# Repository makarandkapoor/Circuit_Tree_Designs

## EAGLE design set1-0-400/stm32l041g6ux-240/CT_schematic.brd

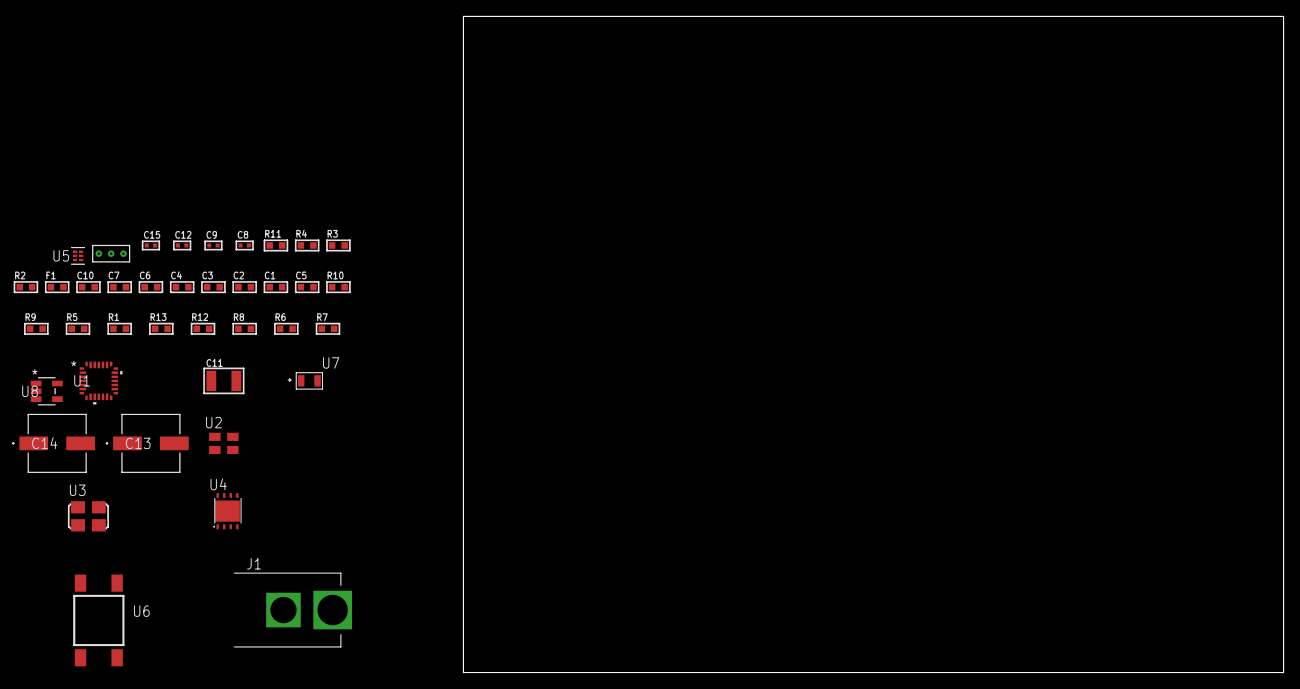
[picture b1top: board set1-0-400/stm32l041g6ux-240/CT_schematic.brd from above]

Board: 2 copper layers, 100.0 x 80.0 mm, 39 parts (0 on the bottom side), 18 nets, no tracks yet.

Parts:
C1, C2, C3, C4: 1e-07; C0603
C5: 4.7e-06; C0603
C6: 1e-08; C0603
C7, C10: 1e-06; C0603
C8, C9, C15: 1e-08; C0402
C11: 1e-05; C1210
C12: 1e-07; C0402
C13, C14: 0.0001; EXV-9H
F1: 240.0; L0603
J1: PJ-037B; PJ-037B_PACKAGE
R1, R5, R9, R10: 10000.0; R0603
R2: 1000.0; R0603
R3: 1600.5; R0603
R4: 4700.0; R0603
R6, R8: 100000.0; R0603
R7: 153694.38; R0603
R11: 9100.0; R0603
R12: 680000.0; R0603
R13: 120000.0; R0603
U1: STM32L041G6U7; UFQFPN28
U2: ASEK-32.768KHz-ECST; ASEK
U3: ASFL1-12MHZ-NCS; ASFL1
U4: LP2951ACSDX/NOPB; WSON-8
U5: TPS3895ADRYR; SON-6
U6: 4-1437565-2; SW_4-1437565-2
U7: Q65110A2395; LGM67K-G1J2-24-Z
U8: nc7sz125m5x; NC7SZ125M5X
U9: Dummy; DUMMY_PACKAGE_78

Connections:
CLK_U1_2: U1.2, U2.3
CLK_U1_6: U1.6, U3.3
GND: C1.2, C2.2, C3.2, C4.2, C5.2, C6.2, C7.2, C8.2, C9.2, C10.2, C11.2, C12.2, C13.2, C14.2, C15.2, J1.2, R2.2, R5.2, R8.2, R11.2, R13.2, U1.16, U1.28, U2.2, U3.2, U4.3, U4.4, U4.PAD, U5.2, U7.C, U8.1, U8.3, U9.1
NET_U1_4: R4.1, U1.4, U8.4
NET_U1_5: C6.1, C7.1, F1.1, U1.5
NET_U1_25: R3.1, U1.25, U7.A
NET_U1_26: R1.1, U1.26, U6.3, U6.4
NET_U1_27: R5.1, U1.27
NET_U4_5: R6.1, U4.5
NET_U4_7: R7.2, R8.1, U4.7
NET_U5_1: R10.1, R11.1, U5.1
NET_U5_3: R12.2, R13.1, U5.3
NET_U5_4: R9.1, U5.4, U8.2
NET_U6_1: R2.1, U6.1, U6.2
PROC_ADC_IN4: U1.10, U9.2
PROC_ADC_IN6: U1.12, U9.3
VCC_S1_5V9: C10.1, C13.1, C14.1, J1.1, U4.8
VCC_TIER1_3V3: C1.1, C2.1, C3.1, C4.1, C5.1, C8.1, C9.1, C11.1, C12.1, C15.1, F1.2, R1.2, R3.2, R4.2, R6.2, R7.1, R9.2, R10.2, R12.1, U1.1, U1.17, U2.4, U3.4, U4.1, U5.6, U8.5

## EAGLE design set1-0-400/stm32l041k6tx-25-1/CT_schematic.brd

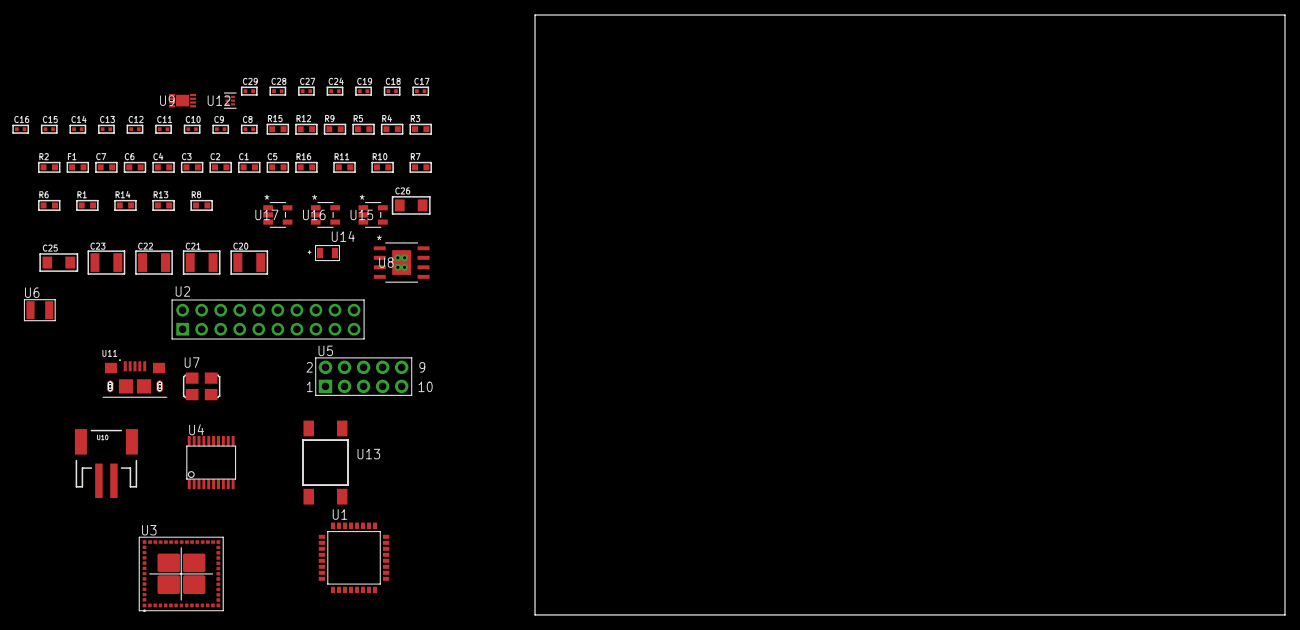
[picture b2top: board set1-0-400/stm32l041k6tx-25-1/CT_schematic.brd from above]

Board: 2 copper layers, 156.9 x 80.0 mm, 63 parts (0 on the bottom side), 41 nets, no tracks yet.

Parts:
C1, C2, C3, C4: 1e-07; C0603
C5: 4.7e-06; C0603
C6: 1e-08; C0603
C7: 1e-06; C0603
C8, C9: 1e-11; C0402
C10, C11, C12, C13, C14, C15, C16, C17, C18, C24: 1e-07; C0402
C19, C27, C28, C29: 1e-08; C0402
C20, C21, C22, C23: 1e-05; C1210
C25, C26: 1e-05; C1206
F1: 240.0; L0603
R1, R6, R7, R10, R11, R16: 10000.0; R0603
R2: 1000.0; R0603
R3: 1600.5; R0603
R4, R5: 4700.0; R0603
R8: 4031.5447154472; R0603
R9: 2200.0; R0603
R12: 9100.0; R0603
R13: 680000.0; R0603
R14: 120000.0; R0603
R15: 2000.0; R0603
U1: STM32L041K6T7; LQFP32
U2: TST-110-05-T-D-RA
U3: MBH7BLZ02-109004
U4: SP3203ECY-L/TR; TSSOP20-I
U5: HTSS-105-01-G-D
U6: ABS07-32.768KHZ-7-T
U7: ASFL1-12MHZ-NCS; ASFL1
U8: MIC5234YME; SOIC-8_EP
U9: MCP73831T-2ACI/MC; DFN8_2X3MC
U10: S2B-PH-SM4-TB(LF)(SN); JST-2-SMD
U11: 10118193-0001LF; FCI_10118193-0001LF
U12: TPS3895ADRYR; SON-6
U13: 4-1437565-2; SW_4-1437565-2
U14: Q65110A2395; LGM67K-G1J2-24-Z
U15, U16, U17: nc7sz125m5x; NC7SZ125M5X

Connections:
CLK_CRYSTAL_U1_2: C8.1, U1.2, U6.1
CLK_CRYSTAL_U1_3: C9.1, U1.3, U6.2
CLK_U1_6: U1.6, U7.3
GND: C1.2, C2.2, C3.2, C4.2, C5.2, C6.2, C7.2, C8.2, C9.2, C10.2, C11.2, C12.2, C13.2, C14.2, C17.2, C18.2, C19.2, C20.2, C21.2, C22.2, C23.2, C24.2, C25.2, C26.2, C27.2, C28.2, C29.2, R2.2, R6.2, R9.2, R12.2, R14.2, R15.2, U1.16, U1.32, U2.4, U2.6, U2.8, U2.10, U2.12, U2.14, U2.16, U2.18, U2.20, U3.1, U3.3, U3.15, U3.27, U3.29, U3.41, U3.42, U3.43, U3.44, U3.45, U3.46, U3.47, U3.48, U3.49, U3.50, U3.52, U3.53, U3.54, U3.55, U3.56, U4.18, U5.9, U7.2, U8.7, U8.EPAD, U9.6, U9.9, U10.2, U11.5, U11.6, U11.7, U11.8, U11.9, U12.2, U14.C, U15.2, U15.3, U16.1, U16.3, U17.1, U17.3
INPUT_USBPOWER_5V: C25.1, R16.2, U9.1, U9.2, U11.1
NET_U1_4: R5.1, U1.4, U17.4
NET_U1_5: C6.1, C7.1, F1.1, U1.5
NET_U1_29: R3.1, U1.29, U14.A
NET_U1_30: R1.1, U1.30, U13.3, U13.4
NET_U1_31: R6.1, U1.31
NET_U3_39: R4.1, U3.39, U16.4
NET_U4_1: C15.1, U4.1
NET_U4_2: C17.1, U4.2
NET_U4_3: C15.2, U4.3
NET_U4_4: C16.1, U4.4
NET_U4_5: C16.2, U4.5
NET_U4_6: C18.1, U4.6
NET_U5_3: U4.14, U5.3
NET_U5_4: U4.13, U5.4
NET_U5_5: U4.17, U5.5
NET_U5_6: U4.16, U5.6
NET_U8_4: R8.2, R9.1, U8.4
NET_U9_5: R16.1, U9.5
NET_U9_8: R15.1, U9.8
NET_U12_1: R11.1, R12.1, U12.1
NET_U12_3: R13.2, R14.1, U12.3
NET_U12_4: R10.1, U12.4, U15.4, U16.2, U17.2
NET_U13_1: R2.1, U13.1, U13.2
PROC_LPUART1_CTS: U1.12, U3.26
PROC_LPUART1_RTS: U1.15, U3.24
PROC_LPUART1_RX: U1.9, U3.25
PROC_LPUART1_TX: U1.8, U3.23
PROC_SYS_SWCLK: U1.24, U2.9
PROC_SYS_SWDIO: U1.23, U2.7
PROC_USART2_CTS: U1.13, U4.8
PROC_USART2_RTS: U1.7, U4.10
PROC_USART2_RX: U1.20, U4.11
PROC_USART2_TX: U1.19, U4.7
RST_OUT_U2_SRESET_B: R7.1, U2.15, U15.1
VCC_S1_3V7: C20.1, C21.1, C26.1, U8.5, U8.8, U9.3, U9.4, U10.1
VCC_TIER1_3V3: C1.1, C2.1, C3.1, C4.1, C5.1, C10.1, C11.1, C12.1, C13.1, C14.1, C19.1, C22.1, C23.1, C24.1, C27.1, C28.1, C29.1, F1.2, R1.2, R3.2, R4.2, R5.2, R7.2, R8.1, R10.2, R11.2, R13.1, U1.1, U1.17, U2.1, U3.28, U4.12, U4.19, U7.4, U8.1, U12.6, U15.5, U16.5, U17.5

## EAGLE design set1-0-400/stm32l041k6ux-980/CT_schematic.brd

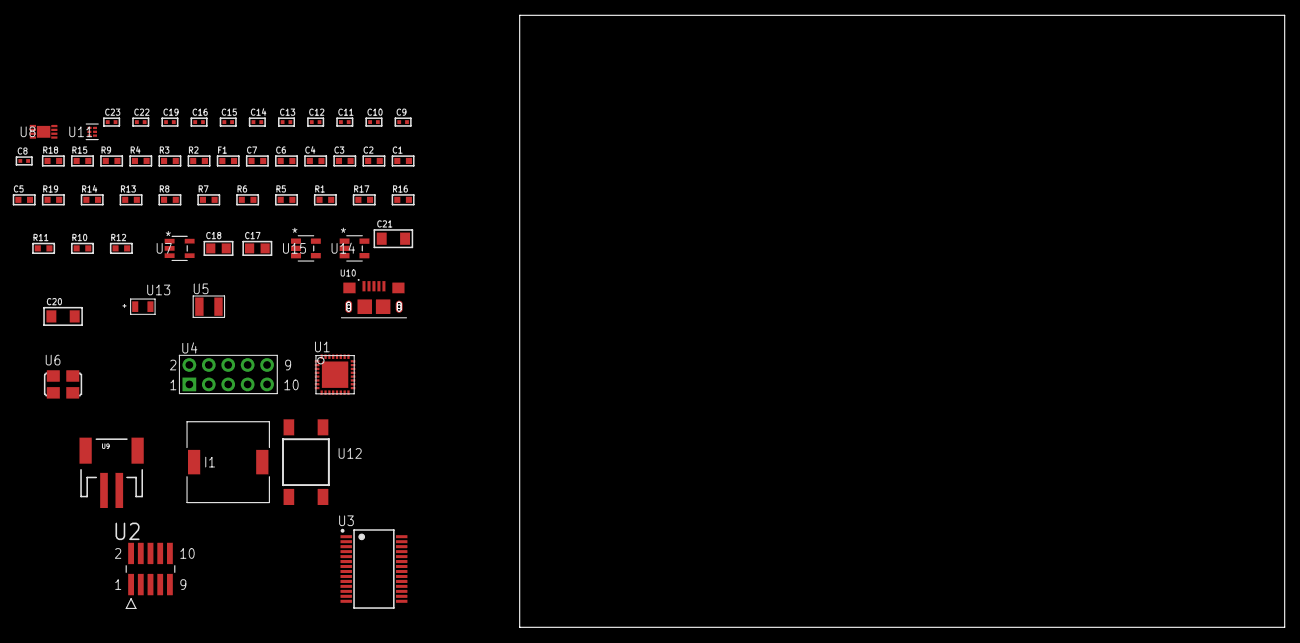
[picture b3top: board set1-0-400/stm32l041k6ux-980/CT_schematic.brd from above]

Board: 2 copper layers, 122.6 x 80.0 mm, 59 parts (0 on the bottom side), 40 nets, no tracks yet.

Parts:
C1, C2, C3, C4: 1e-07; C0603
C5: 4.7e-06; C0603
C6: 1e-08; C0603
C7: 1e-06; C0603
C8, C9: 1e-11; C0402
C10, C11, C12, C13, C14, C15, C19: 1e-07; C0402
C16, C22, C23: 1e-08; C0402
C17, C18: 1e-05; C0805
C20, C21: 1e-05; C1206
F1: 240.0; L0603
I1: 5.2e-06; DR1040
R1, R5, R6, R7, R8, R13, R14, R19: 10000.0; R0603
R2: 1000.0; R0603
R3: 1600.5; R0603
R4: 4700.0; R0603
R9: 5.0; R0603
R10: 100000.0; R0603
R11: 220000.0; R0603
R12: 1000000.0; R0603
R15: 9100.0; R0603
R16: 680000.0; R0603
R17: 120000.0; R0603
R18: 2000.0; R0603
U1: stm32l041K6U7; UFQFPN32
U2: FTSH-105-01-L-DV-K; SAMTEC_FTSH-105-01-L-DV-K
U3: ST3241EBPR; SSOP-28
U4: HTSS-105-01-G-D
U5: ABS07-32.768KHZ-7-T
U6: ASFL1-12MHZ-NCS; ASFL1
U7: ltc3406es5; TSOT-23-5
U8: MCP73831T-2ACI/MC; DFN8_2X3MC
U9: S2B-PH-SM4-TB(LF)(SN); JST-2-SMD
U10: 10118193-0001LF; FCI_10118193-0001LF
U11: TPS3895ADRYR; SON-6
U12: 4-1437565-2; SW_4-1437565-2
U13: Q65110A2395; LGM67K-G1J2-24-Z
U14, U15: nc7sz125m5x; NC7SZ125M5X

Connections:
CLK_CRYSTAL_U1_2: C8.1, U1.2, U5.1
CLK_CRYSTAL_U1_3: C9.1, U1.3, U5.2
CLK_U1_6: U1.6, U6.3
GND: C1.2, C2.2, C3.2, C4.2, C5.2, C6.2, C7.2, C8.2, C9.2, C10.2, C11.2, C14.2, C15.2, C16.2, C17.2, C18.1, C18.2, C19.2, C20.2, C21.2, C22.2, C23.2, R2.2, R5.2, R9.2, R11.2, R15.2, R17.2, R18.2, U1.EPAD, U2.3, U2.5, U3.23, U3.25, U4.9, U6.2, U7.2, U8.6, U8.9, U9.2, U10.5, U10.6, U10.7, U10.8, U10.9, U11.2, U13.C, U14.2, U14.3, U15.1, U15.3
INPUT_USBPOWER_5V: C20.1, R19.2, U8.1, U8.2, U10.1
NET_U1_4: R4.1, U1.4, U15.4
NET_U1_5: C6.1, C7.1, F1.1, U1.5
NET_U1_30: R3.1, U1.30, U13.A
NET_U1_31: R5.1, U1.31
NET_U1_32: R1.1, U1.32, U12.3, U12.4
NET_U2_9: R9.1, U2.9
NET_U3_1: C13.1, U3.1
NET_U3_2: C13.2, U3.2
NET_U3_3: C15.1, U3.3
NET_U3_22: R10.1, U3.22
NET_U3_24: C12.2, U3.24
NET_U3_27: C14.1, U3.27
NET_U3_28: C12.1, U3.28
NET_U4_3: U3.4, U4.3
NET_U4_4: U3.5, U4.4
NET_U4_5: U3.9, U4.5
NET_U4_6: U3.10, U4.6
NET_U7_3: I1.1, U7.3
NET_U7_5: R11.1, R12.1, U7.5
NET_U7_ATNET_3: I1.2, R12.2
NET_U8_5: R19.1, U8.5
NET_U8_8: R18.1, U8.8
NET_U11_1: R14.1, R15.1, U11.1
NET_U11_3: R16.2, R17.1, U11.3
NET_U11_4: R13.1, U11.4, U14.4, U15.2
NET_U12_1: R2.1, U12.1, U12.2
PROC_LPUART1_CTS: U1.12, U3.13
PROC_LPUART1_RTS: U1.15, U3.18
PROC_LPUART1_RX: U1.9, U3.19
PROC_LPUART1_TX: U1.8, U3.14
PROC_SYS_SWCLK: R7.1, U1.24, U2.4
PROC_SYS_SWDIO: R8.1, U1.23, U2.2
RST_OUT_U2_JTAG_RST_B: R6.1, U2.10, U14.1
VCC_S1_3V7: C17.1, C21.1, U7.4, U8.3, U8.4, U9.1
VCC_TIER1_3V3: C1.1, C2.1, C3.1, C4.1, C5.1, C10.1, C11.1, C16.1, C18.2, C19.1, C22.1, C23.1, F1.2, I1.2, R1.2, R3.2, R4.2, R6.2, R7.2, R8.2, R10.2, R12.2, R13.2, R14.2, R16.1, U1.1, U1.17, U2.1, U3.26, U6.4, U11.6, U14.5, U15.5

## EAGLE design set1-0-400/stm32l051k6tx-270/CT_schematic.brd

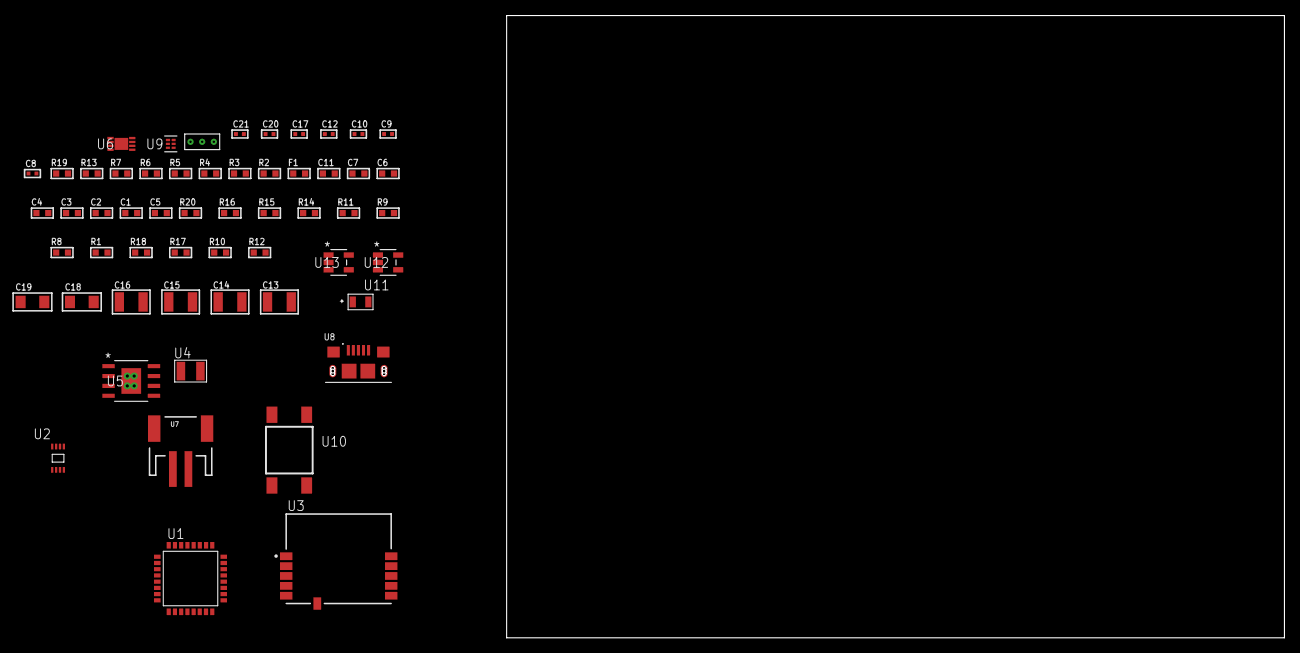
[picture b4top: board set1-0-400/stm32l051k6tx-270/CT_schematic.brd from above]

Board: 2 copper layers, 122.6 x 80.0 mm, 56 parts (0 on the bottom side), 28 nets, no tracks yet.

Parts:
C1, C2, C3, C4: 1e-07; C0603
C5: 4.7e-06; C0603
C6: 1e-08; C0603
C7, C11: 1e-06; C0603
C8, C9: 1e-11; C0402
C10, C20, C21: 1e-08; C0402
C12, C17: 1e-07; C0402
C13, C14, C15, C16: 1e-05; C1210
C18, C19: 1e-05; C1206
F1: 240.0; L0603
R1, R8, R9, R14, R15, R20: 10000.0; R0603
R2: 1000.0; R0603
R3: 910.0; R0603
R4, R5: 4700.0; R0603
R6, R7, R13: 2200.0; R0603
R10: 100000.0; R0603
R11: 47000.0; R0603
R12: 1402.2764227642; R0603
R16: 82000.0; R0603
R17: 300000.0; R0603
R18: 120000.0; R0603
R19: 2000.0; R0603
U1: STM32L051K6T6; LQFP32
U2: 24AA00T-I/MNY; TDFN-8/6MM
U3: SPBTLE-RF; XCVR_SPBTLE-RF
U4: ABS07-32.768KHZ-7-T
U5: MIC5234YME; SOIC-8_EP
U6: MCP73831T-2ACI/MC; DFN8_2X3MC
U7: S2B-PH-SM4-TB(LF)(SN); JST-2-SMD
U8: 10118193-0001LF; FCI_10118193-0001LF
U9: TPS3895ADRYR; SON-6
U10: 4-1437565-2; SW_4-1437565-2
U11: Q65110A2395; LGM67K-G1J2-24-Z
U12, U13: nc7sz125m5x; NC7SZ125M5X
U14: Dummy; DUMMY_PACKAGE_116

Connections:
CLK_CRYSTAL_U1_2: C8.1, U1.2, U4.1
CLK_CRYSTAL_U1_3: C9.1, U1.3, U4.2
GND: C1.2, C2.2, C3.2, C4.2, C5.2, C6.2, C7.2, C8.2, C9.2, C10.2, C11.2, C12.2, C13.2, C14.2, C15.2, C16.2, C17.2, C18.2, C19.2, C20.2, C21.2, R2.2, R8.2, R10.2, R11.2, R13.2, R16.2, R18.2, R19.2, U1.16, U1.32, U2.4, U3.6, U5.7, U5.EPAD, U6.6, U6.9, U7.2, U8.5, U8.6, U8.7, U8.8, U8.9, U9.2, U11.C, U12.1, U12.3, U13.1, U13.3, U14.1
INPUT_USBPOWER_5V: C18.1, R20.2, U6.1, U6.2, U8.1
NET_U1_4: R5.1, U1.4, U13.4
NET_U1_5: C6.1, C7.1, F1.1, U1.5
NET_U1_27: R3.1, U1.27, U11.A
NET_U1_28: R1.1, U1.28, U10.3, U10.4
NET_U1_29: R6.1, U1.29, U2.6
NET_U1_30: R7.1, U1.30, U2.5
NET_U1_31: R8.1, U1.31
NET_U3_11: R4.1, U3.11, U12.4
NET_U5_4: R12.2, R13.1, U5.4
NET_U6_5: R20.1, U6.5
NET_U6_8: R19.1, U6.8
NET_U9_1: R15.1, R16.1, U9.1
NET_U9_3: R17.2, R18.1, U9.3
NET_U9_4: R14.1, U9.4, U12.2, U13.2
NET_U10_1: R2.1, U10.1, U10.2
PROC_GPIO_TO_U3_SPI_IRQ: R11.1, U1.6, U3.4
PROC_SPI1_MISO: U1.12, U3.8
PROC_SPI1_MOSI: U1.13, U3.9
PROC_SPI1_NSS: R9.1, U1.10, U3.10
PROC_SPI1_SCK: R10.1, U1.11, U3.7
PROC_TIM2_CH3: U1.8, U14.3
PROC_TIM2_CH4: U1.9, U14.2
VCC_S1_3V7: C13.1, C14.1, C19.1, U5.5, U5.8, U6.3, U6.4, U7.1
VCC_TIER1_1V8: C1.1, C2.1, C3.1, C4.1, C5.1, C10.1, C11.1, C12.1, C15.1, C16.1, C17.1, C20.1, C21.1, F1.2, R1.2, R3.2, R4.2, R5.2, R6.2, R7.2, R9.2, R12.1, R14.2, R15.2, R17.1, U1.1, U1.17, U2.8, U3.5, U5.1, U9.6, U12.5, U13.5

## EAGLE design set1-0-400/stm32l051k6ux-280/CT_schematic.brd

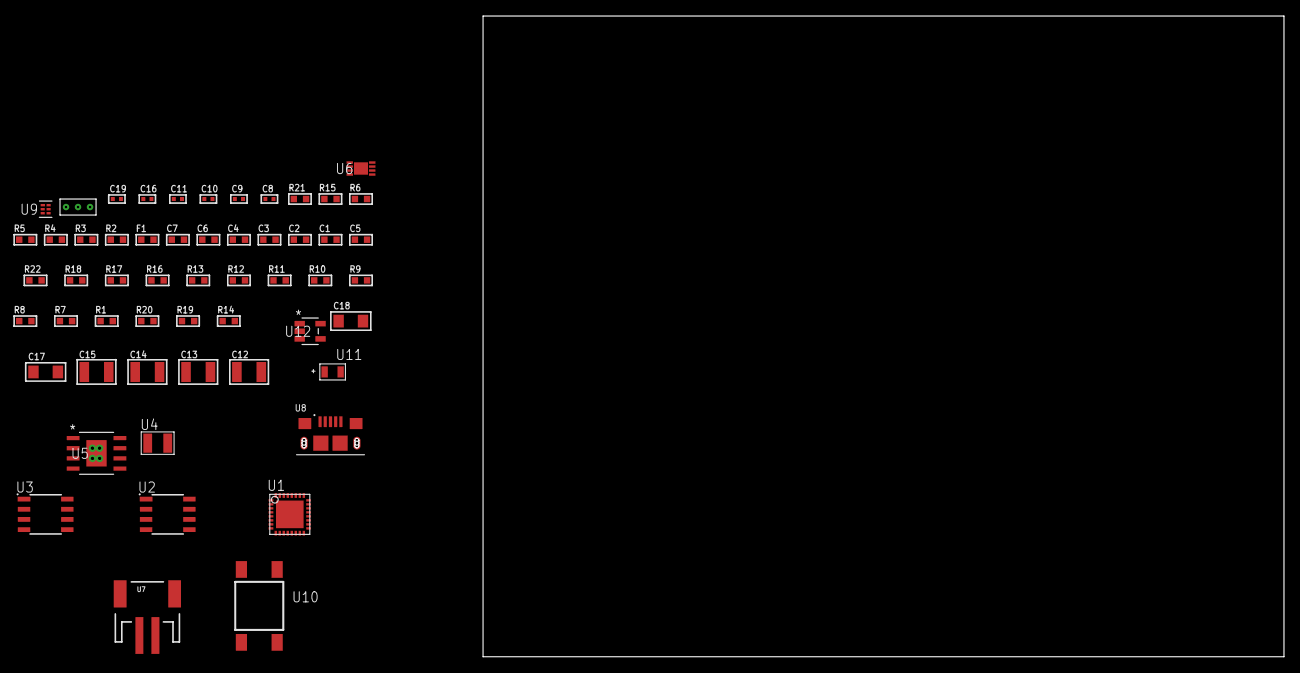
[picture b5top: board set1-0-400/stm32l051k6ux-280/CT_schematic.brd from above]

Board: 2 copper layers, 122.6 x 80.0 mm, 55 parts (0 on the bottom side), 31 nets, no tracks yet.

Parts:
C1, C2, C3, C4: 1e-07; C0603
C5: 4.7e-06; C0603
C6: 1e-08; C0603
C7: 1e-06; C0603
C8, C9: 1e-11; C0402
C10, C11, C19: 1e-08; C0402
C12, C13, C14, C15: 1e-05; C1210
C16: 1e-07; C0402
C17, C18: 1e-05; C1206
F1: 240.0; L0603
R1, R7, R8, R9, R10, R11, R12, R13, R16, R17, R22: 10000.0; R0603
R2: 1000.0; R0603
R3: 910.0; R0603
R4: 4700.0; R0603
R5, R6, R15: 2200.0; R0603
R14: 1402.2764227642; R0603
R18: 82000.0; R0603
R19: 300000.0; R0603
R20: 120000.0; R0603
R21: 2000.0; R0603
U1: STM32L051K6U6; UFQFPN32
U2: AT25080B-SSHL-T; SOIC-8
U3: 24AA1025T-I/SN; SOIC-8
U4: ABS07-32.768KHZ-7-T
U5: MIC5234YME; SOIC-8_EP
U6: MCP73831T-2ACI/MC; DFN8_2X3MC
U7: S2B-PH-SM4-TB(LF)(SN); JST-2-SMD
U8: 10118193-0001LF; FCI_10118193-0001LF
U9: TPS3895ADRYR; SON-6
U10: 4-1437565-2; SW_4-1437565-2
U11: Q65110A2395; LGM67K-G1J2-24-Z
U12: nc7sz125m5x; NC7SZ125M5X
U13: Dummy; DUMMY_PACKAGE_115

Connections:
CLK_CRYSTAL_U1_2: C8.1, U1.2, U4.1
CLK_CRYSTAL_U1_3: C9.1, U1.3, U4.2
GND: C1.2, C2.2, C3.2, C4.2, C5.2, C6.2, C7.2, C8.2, C9.2, C10.2, C11.2, C12.2, C13.2, C14.2, C15.2, C16.2, C17.2, C18.2, C19.2, R2.2, R7.2, R15.2, R18.2, R20.2, R21.2, U1.EPAD, U2.4, U3.4, U5.7, U5.EPAD, U6.6, U6.9, U7.2, U8.5, U8.6, U8.7, U8.8, U8.9, U9.2, U11.C, U12.1, U12.3, U13.1
INPUT_USBPOWER_5V: C17.1, R22.2, U6.1, U6.2, U8.1
NET_U1_4: R4.1, U1.4, U12.4
NET_U1_5: C6.1, C7.1, F1.1, U1.5
NET_U1_28: R3.1, U1.28, U11.A
NET_U1_29: R5.1, U1.29, U3.6
NET_U1_30: R6.1, U1.30, U3.5
NET_U1_31: R7.1, U1.31
NET_U1_32: R1.1, U1.32, U10.3, U10.4
NET_U2_3: R8.1, U2.3
NET_U2_7: R10.1, U2.7
NET_U3_1: R12.1, U3.1
NET_U3_2: R13.1, U3.2
NET_U3_3: R11.1, U3.3
NET_U5_4: R14.2, R15.1, U5.4
NET_U6_5: R22.1, U6.5
NET_U6_8: R21.1, U6.8
NET_U9_1: R17.1, R18.1, U9.1
NET_U9_3: R19.2, R20.1, U9.3
NET_U9_4: R16.1, U9.4, U12.2
NET_U10_1: R2.1, U10.1, U10.2
PROC_SPI1_MISO: U1.12, U2.2
PROC_SPI1_MOSI: U1.13, U2.5
PROC_SPI1_NSS: R9.1, U1.10, U2.1
PROC_SPI1_SCK: U1.11, U2.6
PROC_TIM2_CH3: U1.8, U13.3
PROC_TIM2_CH4: U1.9, U13.2
VCC_S1_3V7: C12.1, C13.1, C18.1, U5.5, U5.8, U6.3, U6.4, U7.1
VCC_TIER1_1V8: C1.1, C2.1, C3.1, C4.1, C5.1, C10.1, C11.1, C14.1, C15.1, C16.1, C19.1, F1.2, R1.2, R3.2, R4.2, R5.2, R6.2, R8.2, R9.2, R10.2, R11.2, R12.2, R13.2, R14.1, R16.2, R17.2, R19.1, U1.1, U1.17, U2.8, U3.7, U3.8, U5.1, U9.6, U12.5

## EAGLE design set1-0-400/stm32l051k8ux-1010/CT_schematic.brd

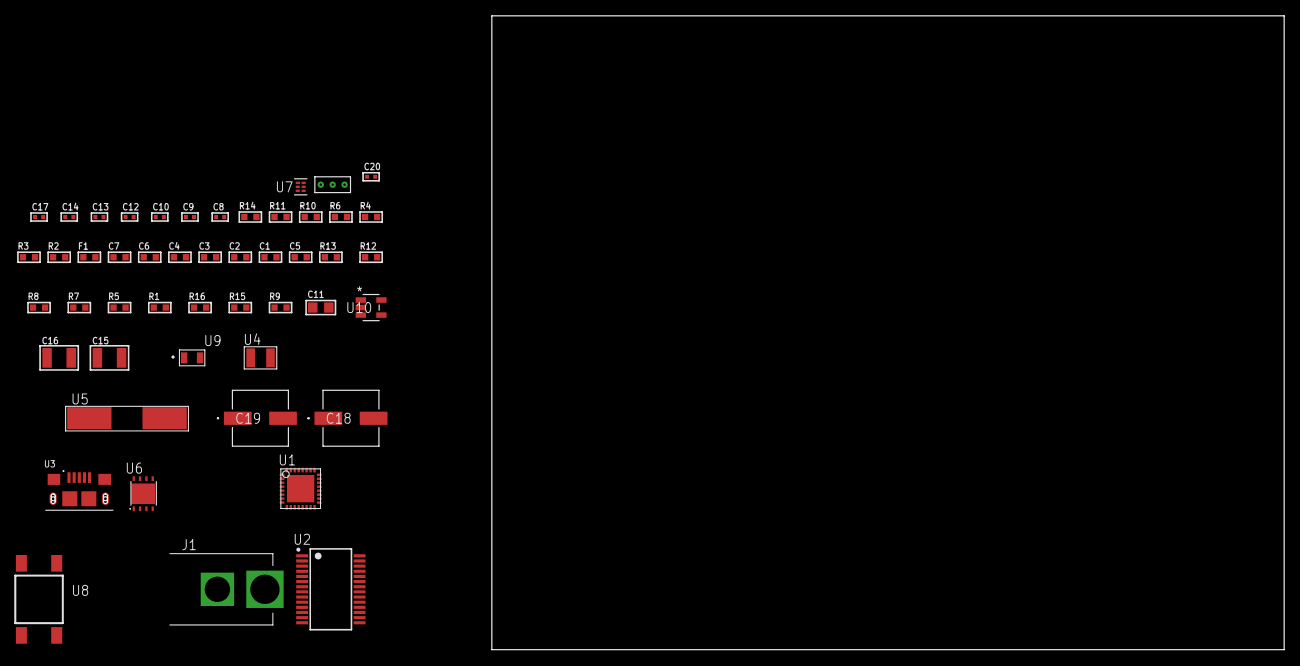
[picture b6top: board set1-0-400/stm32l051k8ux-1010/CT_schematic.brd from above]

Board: 2 copper layers, 155.6 x 80.0 mm, 49 parts (0 on the bottom side), 31 nets, no tracks yet.

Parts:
C1, C2, C3, C4: 1e-07; C0603
C5: 4.7e-06; C0603
C6: 1e-08; C0603
C7: 1e-06; C0603
C8, C9: 1e-11; C0402
C10, C12, C13, C17: 1e-07; C0402
C11: 4.7e-06; C0805
C14, C20: 1e-08; C0402
C15, C16: 1e-05; C1210
C18, C19: 0.0001; EXV-9H
F1: 240.0; L0603
J1: PJ-037B; PJ-037B_PACKAGE
R1, R5, R7, R8, R12, R13: 10000.0; R0603
R2, R11: 1000.0; R0603
R3: 1600.5; R0603
R4, R6: 4700.0; R0603
R9: 100000.0; R0603
R10: 2231.0; R0603
R14: 9100.0; R0603
R15: 680000.0; R0603
R16: 120000.0; R0603
U1: STM32L051K8U3; UFQFPN32
U2: FT232RL-REEL; SSOP-28
U3: 10118193-0001LF; FCI_10118193-0001LF
U4: ABS07-32.768KHZ-7-T
U5: ABLS-12.000MHZ-B4-T
U6: LP3878SDX-ADJ/NOPB; WSON-8
U7: TPS3895ADRYR; SON-6
U8: 4-1437565-2; SW_4-1437565-2
U9: Q65110A2395; LGM67K-G1J2-24-Z
U10: nc7sz125m5x; NC7SZ125M5X
U11: Dummy; DUMMY_PACKAGE_97

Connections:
CLK_CRYSTAL_U1_2: C8.1, U1.2, U4.1
CLK_CRYSTAL_U1_3: C9.1, U1.3, U4.2
CLK_CRYSTAL_U2_27: U2.27, U5.1
CLK_CRYSTAL_U2_28: U2.28, U5.2
GND: C1.2, C2.2, C3.2, C4.2, C5.2, C6.2, C7.2, C8.2, C9.2, C10.2, C11.2, C12.2, C13.2, C14.2, C15.2, C16.2, C17.2, C18.2, C19.2, C20.2, J1.2, R2.2, R5.2, R8.2, R11.2, R14.2, R16.2, U1.EPAD, U2.7, U2.18, U2.21, U2.25, U2.26, U3.5, U3.6, U3.7, U3.8, U3.9, U6.3, U6.PAD, U7.2, U9.C, U10.1, U10.3, U11.1
NET_U1_4: R4.1, U1.4, U10.4
NET_U1_5: C6.1, C7.1, F1.1, U1.5
NET_U1_30: R3.1, U1.30, U9.A
NET_U1_31: R5.1, U1.31
NET_U1_32: R1.1, U1.32, U8.3, U8.4
NET_U2_14: R7.1, U2.14
NET_U2_17: C12.1, U2.17
NET_U2_19: R8.1, U2.19
NET_U3_1: R6.1, U3.1
NET_U3_2: U2.16, U3.2
NET_U3_3: U2.15, U3.3
NET_U6_1: C14.1, U6.1
NET_U6_6: R10.2, R11.1, U6.6
NET_U6_8: R9.1, U6.8
NET_U7_1: R13.1, R14.1, U7.1
NET_U7_3: R15.2, R16.1, U7.3
NET_U7_4: R12.1, U7.4, U10.2
NET_U8_1: R2.1, U8.1, U8.2
PROC_ADC_IN4: U1.10, U11.2
PROC_ADC_IN6: U1.12, U11.3
PROC_USART1_CTS: U1.21, U2.3
PROC_USART1_RTS: U1.22, U2.11
PROC_USART1_RX: U1.20, U2.1
PROC_USART1_TX: U1.19, U2.5
VCC_S1_13V6: C15.1, C18.1, C19.1, J1.1, R9.2, U6.4
VCC_TIER1_3V3: C1.1, C2.1, C3.1, C4.1, C5.1, C10.1, C11.1, C13.1, C16.1, C17.1, C20.1, F1.2, R1.2, R3.2, R4.2, R7.2, R10.1, R12.2, R13.2, R15.1, U1.1, U1.17, U2.4, U2.20, U6.5, U7.6, U10.5

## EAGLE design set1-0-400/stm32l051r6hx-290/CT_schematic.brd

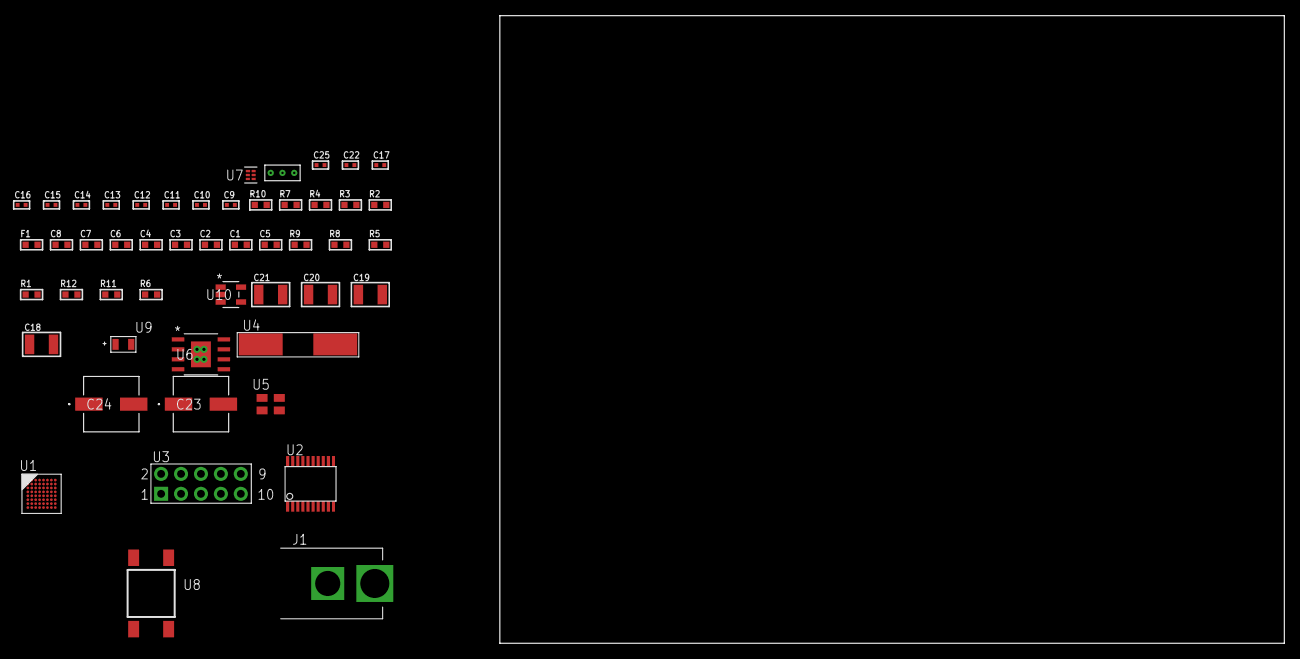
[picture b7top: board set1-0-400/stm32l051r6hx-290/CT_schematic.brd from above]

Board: 2 copper layers, 100.0 x 80.0 mm, 50 parts (0 on the bottom side), 32 nets, no tracks yet.

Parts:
C1, C2, C3, C4, C6: 1e-07; C0603
C5: 4.7e-06; C0603
C7: 1e-08; C0603
C8: 1e-06; C0603
C9, C10: 1e-11; C0402
C11, C12, C13, C14, C15, C16, C22: 1e-07; C0402
C17, C25: 1e-08; C0402
C18, C19, C20, C21: 1e-05; C1210
C23, C24: 0.0001; EXV-9H
F1: 240.0; L0603
J1: PJ-037B; PJ-037B_PACKAGE
R1, R5, R8, R9: 10000.0; R0603
R2: 1000.0; R0603
R3: 1600.5; R0603
R4: 4700.0; R0603
R6: 4031.5447154472; R0603
R7: 2200.0; R0603
R10: 9100.0; R0603
R11: 680000.0; R0603
R12: 120000.0; R0603
U1: STM32L051R6H6; TFBGA64
U2: SP3203ECY-L/TR; TSSOP20-I
U3: HTSS-105-01-G-D
U4: ABLS-25.000MHZ-B2F-T
U5: ASEK-32.768KHz-ECST; ASEK
U6: MIC5234YME; SOIC-8_EP
U7: TPS3895ADRYR; SON-6
U8: 4-1437565-2; SW_4-1437565-2
U9: Q65110A2395; LGM67K-G1J2-24-Z
U10: nc7sz125m5x; NC7SZ125M5X
U11: Dummy; DUMMY_PACKAGE_101

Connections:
CLK_CRYSTAL_U1_C1: C9.1, U1.C1, U4.1
CLK_CRYSTAL_U1_D1: C10.1, U1.D1, U4.2
CLK_U1_A1: U1.A1, U5.3
GND: C1.2, C2.2, C3.2, C4.2, C5.2, C6.2, C7.2, C8.2, C9.2, C10.2, C11.2, C12.2, C15.2, C16.2, C17.2, C18.2, C19.2, C20.2, C21.2, C22.2, C23.2, C24.2, C25.2, J1.2, R2.2, R5.2, R7.2, R10.2, R12.2, U1.C2, U1.D4, U1.D5, U1.D6, U1.F1, U2.18, U3.9, U5.2, U6.7, U6.EPAD, U7.2, U9.C, U10.1, U10.3, U11.1
NET_U1_B4: R5.1, U1.B4
NET_U1_E1: R4.1, U1.E1, U10.4
NET_U1_H1: C7.1, C8.1, F1.1, U1.G1, U1.H1
NET_U1_H7: R3.1, U1.H7, U9.A
NET_U1_H8: R1.1, U1.H8, U8.3, U8.4
NET_U2_1: C13.1, U2.1
NET_U2_2: C15.1, U2.2
NET_U2_3: C13.2, U2.3
NET_U2_4: C14.1, U2.4
NET_U2_5: C14.2, U2.5
NET_U2_6: C16.1, U2.6
NET_U3_3: U2.14, U3.3
NET_U3_4: U2.13, U3.4
NET_U3_5: U2.17, U3.5
NET_U3_6: U2.16, U3.6
NET_U6_4: R6.2, R7.1, U6.4
NET_U7_1: R9.1, R10.1, U7.1
NET_U7_3: R11.2, R12.1, U7.3
NET_U7_4: R8.1, U7.4, U10.2
NET_U8_1: R2.1, U8.1, U8.2
PROC_ADC_IN3: U1.G3, U11.2
PROC_ADC_IN4: U1.H3, U11.3
PROC_LPUART1_CTS: U1.G4, U2.8
PROC_LPUART1_RTS: U1.B5, U2.10
PROC_LPUART1_RX: U1.B6, U2.11
PROC_LPUART1_TX: U1.B7, U2.7
VCC_S1_12V2: C18.1, C19.1, C23.1, C24.1, J1.1, U6.5, U6.8
VCC_TIER1_3V3: C1.1, C2.1, C3.1, C4.1, C5.1, C6.1, C11.1, C12.1, C17.1, C20.1, C21.1, C22.1, C25.1, F1.2, R1.2, R3.2, R4.2, R6.1, R8.2, R9.2, R11.1, U1.B2, U1.D2, U1.E4, U1.E5, U1.E6, U2.12, U2.19, U5.4, U6.1, U7.6, U10.5

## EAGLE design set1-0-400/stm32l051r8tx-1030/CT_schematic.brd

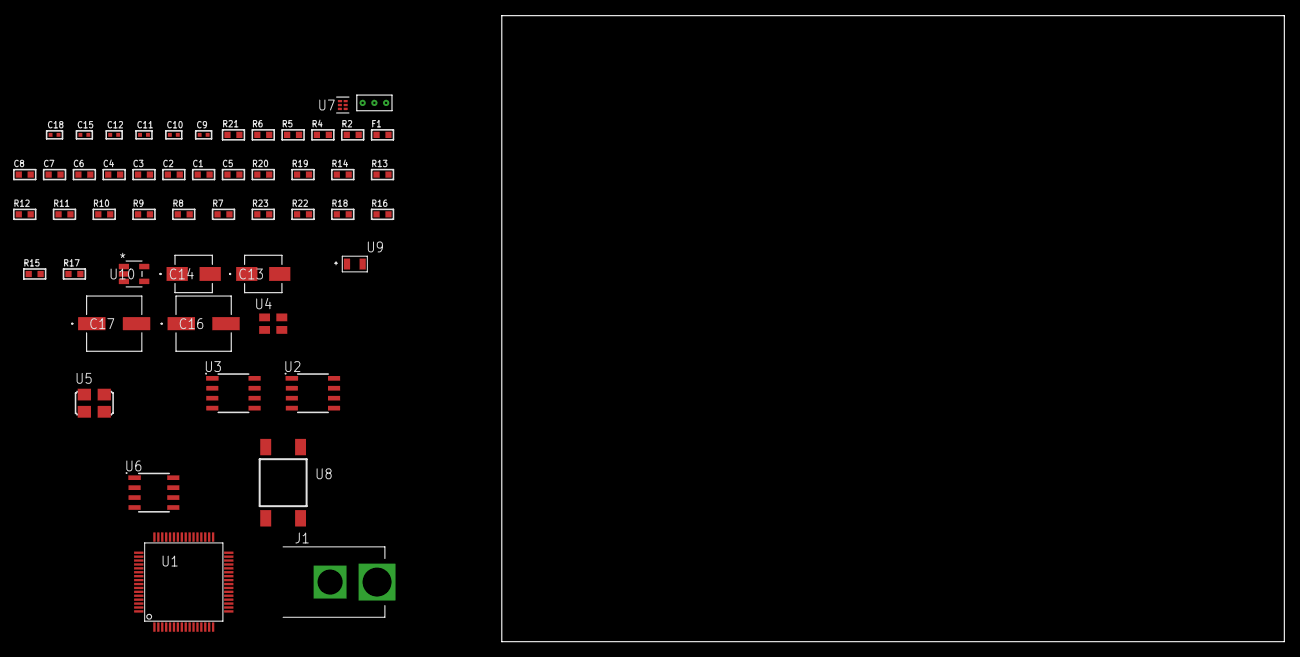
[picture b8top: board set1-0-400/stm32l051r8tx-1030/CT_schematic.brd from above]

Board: 2 copper layers, 100.0 x 80.0 mm, 52 parts (0 on the bottom side), 30 nets, no tracks yet.

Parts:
C1, C2, C3, C4, C6: 1e-07; C0603
C5: 4.7e-06; C0603
C7: 1e-08; C0603
C8: 1e-06; C0603
C9, C11, C12, C18: 1e-08; C0402
C10, C15: 1e-07; C0402
C13: 1e-06; EXV-9B
C14: 2.2e-06; EXV-9B
C16, C17: 0.0001; EXV-9H
F1: 240.0; L0603
J1: PJ-037B; PJ-037B_PACKAGE
R2: 1000.0; R0603
R4: 4700.0; R0603
R5, R6: 2200.0; R0603
R7, R8, R9, R10, R11, R12, R13, R14, R19, R20: 10000.0; R0603
R15, R16, R18: 100000.0; R0603
R17: 164658.62; R0603
R21: 9100.0; R0603
R22: 680000.0; R0603
R23: 120000.0; R0603
U1: STM32L051R8T7; LQFP64
U2: AT25020B-SSHL-T; SOIC-8
U3: TMP75BID; SOIC-8
U4: ASEK-32.768KHz-ECST; ASEK
U5: ASFL1-25MHZ-NCS; ASFL1
U6: LP2954AIMX/NOPB; LP2954
U7: TPS3895ADRYR; SON-6
U8: 4-1437565-2; SW_4-1437565-2
U9: Q65110A2395; LGM67K-G1J2-24-Z
U10: nc7sz125m5x; NC7SZ125M5X
U11: Dummy; DUMMY_PACKAGE_112

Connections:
CLK_U1_3: U1.3, U4.3
CLK_U1_5: U1.5, U5.3
GND: C1.2, C2.2, C3.2, C4.2, C5.2, C6.2, C7.2, C8.2, C9.2, C10.2, C11.2, C12.2, C13.2, C14.2, C15.2, C16.2, C17.2, C18.2, J1.2, R2.2, R7.2, R12.2, R13.2, R18.2, R21.2, R23.2, U1.12, U1.18, U1.31, U1.47, U1.63, U2.4, U3.4, U4.2, U5.2, U6.4, U7.2, U9.C, U10.1, U10.3, U11.1
NET_U1_7: R4.1, U1.7, U10.4
NET_U1_13: C7.1, C8.1, F1.1, U1.13
NET_U1_58: R5.1, U1.58, U3.2
NET_U1_59: R6.1, U1.59, U3.1
NET_U1_60: R7.1, U1.60
NET_U1_62: U8.3, U8.4
NET_U2_3: R8.1, U2.3
NET_U2_7: R10.1, U2.7
NET_U3_3: R11.1, U3.3
NET_U3_5: R14.1, U3.5
NET_U3_6: R13.1, U3.6
NET_U3_7: R12.1, U3.7
NET_U6_3: R16.1, U6.3
NET_U6_5: R15.1, U6.5
NET_U6_7: R17.2, R18.1, U6.7
NET_U7_1: R20.1, R21.1, U7.1
NET_U7_3: R22.2, R23.1, U7.3
NET_U7_4: R19.1, U7.4, U10.2
NET_U8_1: R2.1, U8.1, U8.2
PROC_ADC_IN3: U1.17, U11.3
PROC_ADC_IN13: U1.11, U11.2
PROC_SPI1_MISO: U1.22, U2.2
PROC_SPI1_MOSI: U1.23, U2.5
PROC_SPI1_NSS: R9.1, U1.20, U2.1
PROC_SPI1_SCK: U1.21, U2.6
VCC_S1_15V8: C13.1, C16.1, C17.1, J1.1, R16.2, U6.8
VCC_TIER1_3V3: C1.1, C2.1, C3.1, C4.1, C5.1, C6.1, C9.1, C10.1, C11.1, C12.1, C14.1, C15.1, C18.1, F1.2, R4.2, R5.2, R6.2, R8.2, R9.2, R10.2, R11.2, R14.2, R15.2, R17.1, R19.2, R20.2, R22.1, U1.1, U1.19, U1.32, U1.48, U1.64, U2.8, U3.8, U4.4, U5.4, U6.1, U7.6, U10.5
